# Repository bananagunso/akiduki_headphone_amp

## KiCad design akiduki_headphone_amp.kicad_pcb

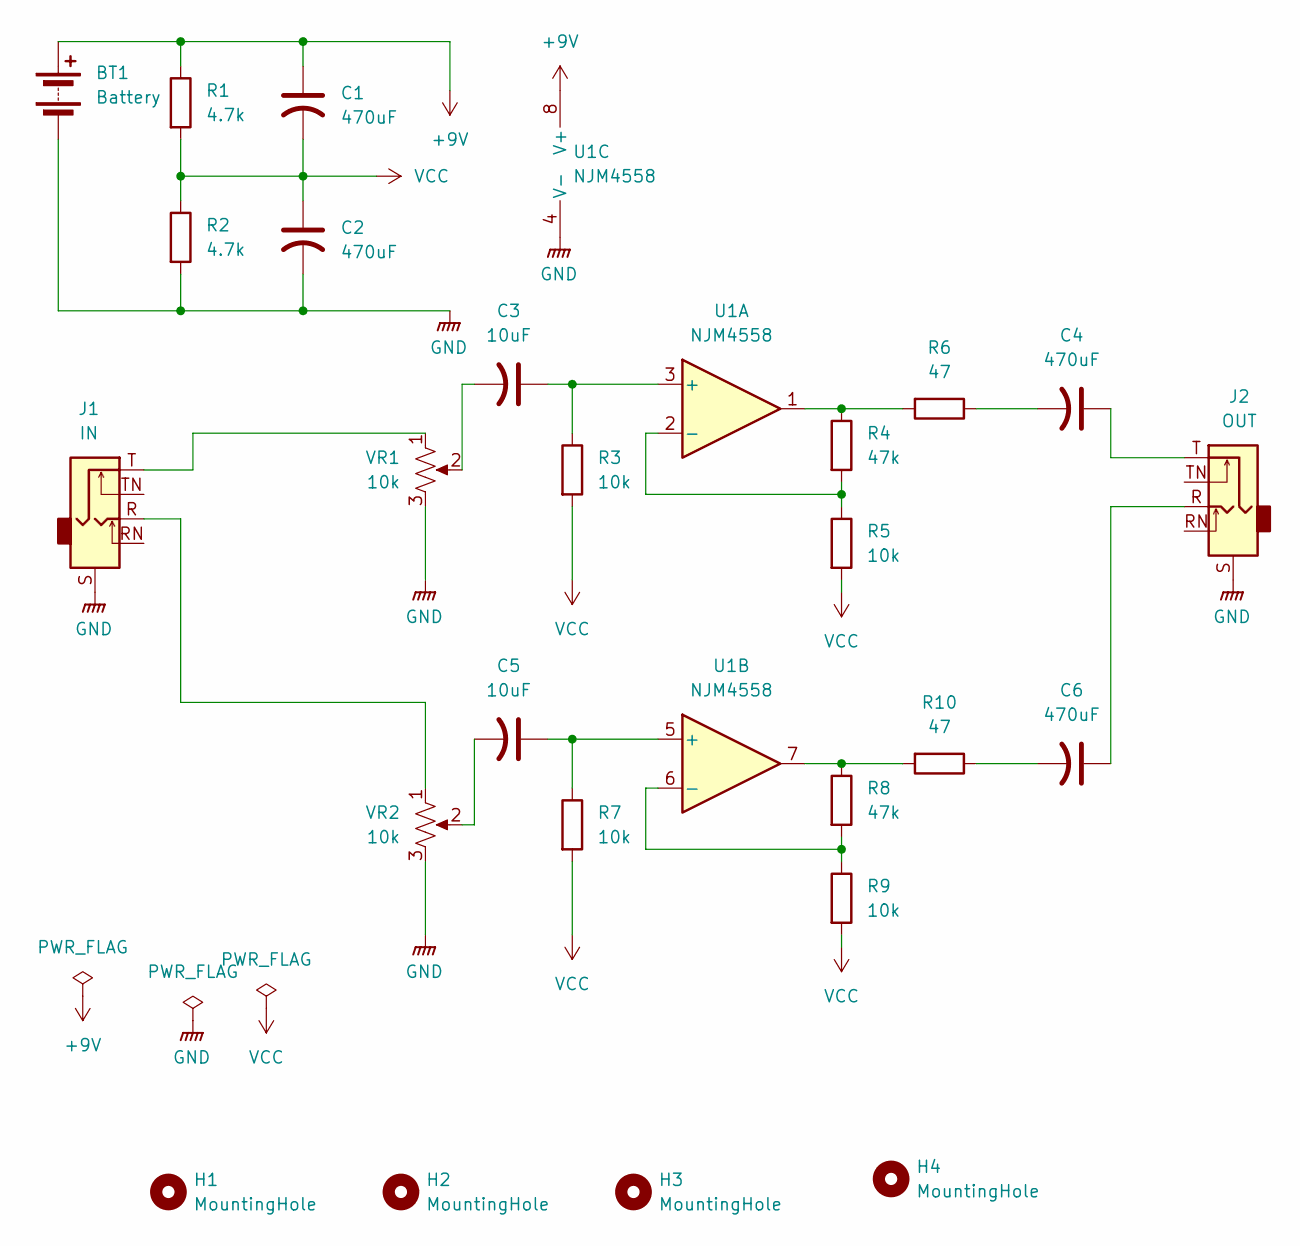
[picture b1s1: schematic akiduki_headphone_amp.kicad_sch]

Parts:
BT1: Battery; JST_XH_B2B-XH-A_1x02_P2.50mm_Vertical
C1, C2, C4, C6: 470uF; CP_Radial_D8.0mm_P2.50mm
C3, C5: 10uF; CP_Radial_D6.3mm_P2.50mm
H1, H2, H3, H4: MountingHole; MountingHole_3.2mm_M3
J1: IN; Jack_3.5mm_CUI_SJ1-3515N_Horizontal
J2: OUT; Jack_3.5mm_CUI_SJ1-3515N_Horizontal
R1, R2: 4.7k; R_Axial_DIN0204_L3.6mm_D1.6mm_P7.62mm_Horizontal
R3, R5, R7, R9: 10k; R_Axial_DIN0204_L3.6mm_D1.6mm_P7.62mm_Horizontal
R4, R8: 47k; R_Axial_DIN0204_L3.6mm_D1.6mm_P7.62mm_Horizontal
R6, R10: 47; R_Axial_DIN0204_L3.6mm_D1.6mm_P7.62mm_Horizontal
U1: NJM4558; CERDIP-8_W7.62mm_SideBrazed
VR1, VR2: 10k; Potentiometer_Piher_PT-10-V05_Vertical

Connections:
+9V: BT1.1 (+), C1.1, R1.1, U1.8 (V+)
GND: BT1.2 (-), C2.2, J1.S, J2.S, R2.2, U1.4 (V-), VR1.3, VR2.3
unnamed: C3.2, VR1.2
unnamed: C4.1, J2.T
unnamed: C4.2, R6.1
unnamed: C5.2, VR2.2
unnamed: C6.1, J2.R
unnamed: C6.2, R10.1
unnamed: J1.R, VR2.1
unnamed: J1.T, VR1.1
unnamed: R4.1, R6.2, U1.1
unnamed: R8.1, R10.2, U1.7
unnamed: C3.1, R3.1, U1.3 (+)
unnamed: R4.2, R5.1, U1.2 (-)
unnamed: C5.1, R7.1, U1.5 (+)
unnamed: R8.2, R9.1, U1.6 (-)
VCC: C1.2, C2.1, R1.2, R2.1, R3.2, R5.2, R7.2, R9.2

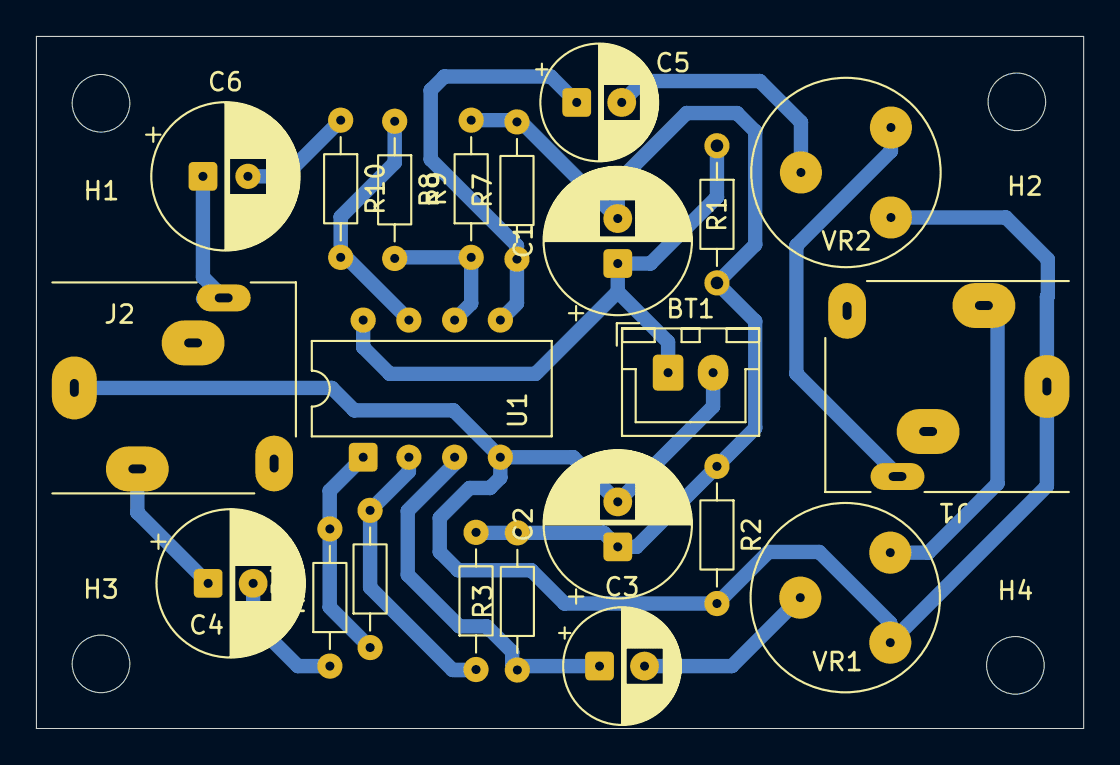
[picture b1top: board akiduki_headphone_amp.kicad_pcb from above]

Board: 2 copper layers, 58.2 x 38.4 mm, 26 parts (0 on the bottom side), 17 nets.

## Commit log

2025-10-24 Initial
2025-10-24 パーツ間を詰めた
2025-10-24 gndベタ
2025-10-24 gndベタ取消
